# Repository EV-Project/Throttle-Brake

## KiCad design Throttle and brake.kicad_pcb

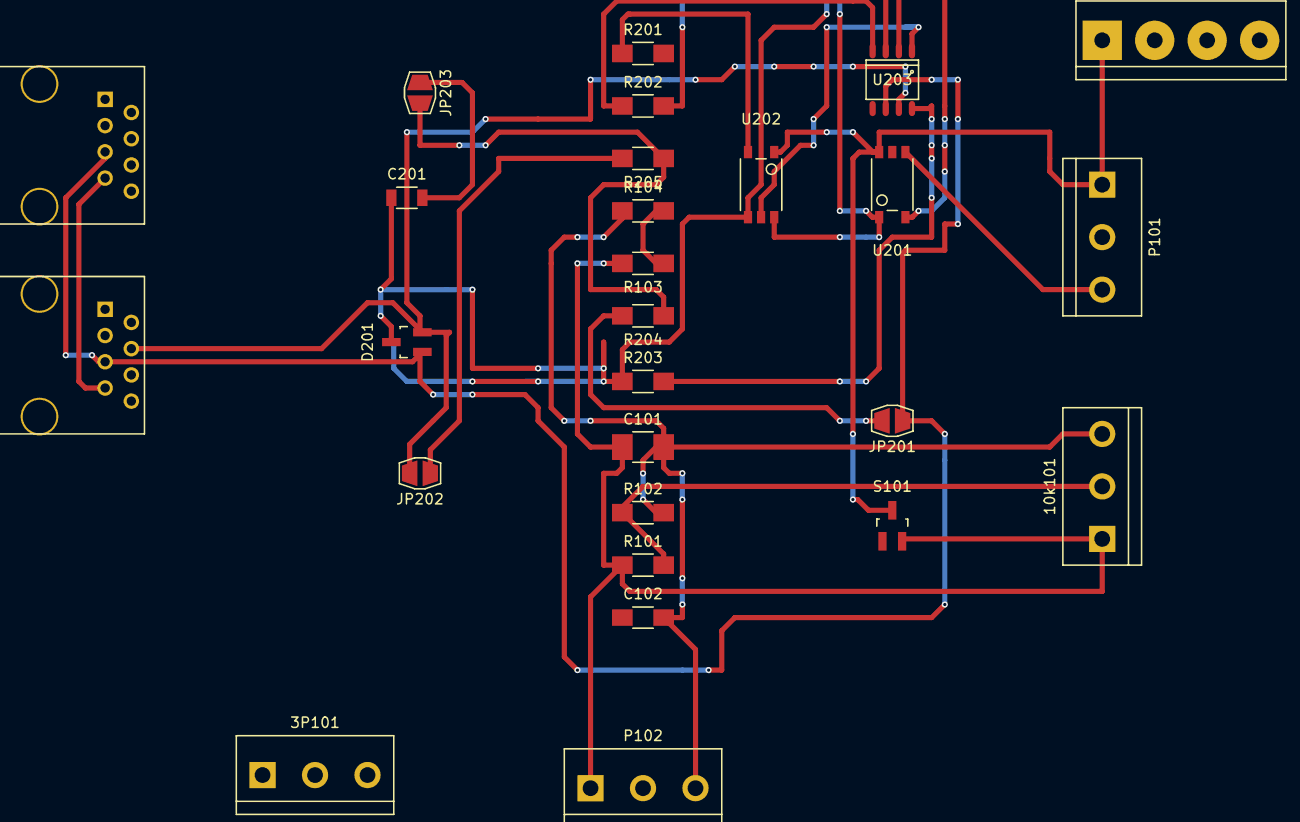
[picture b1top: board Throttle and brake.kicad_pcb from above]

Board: 2 copper layers, 27 parts (0 on the bottom side), 21 nets.

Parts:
3P101: Lever; bornier3
4P101: Ignition Switch; bornier4
10k101: POT; bornier3
C101: 10 uF; C_1210_HandSoldering
C102: 0.1 uF; C_1206_HandSoldering
C201: 4.7nF; C_1206
D201: PESD1CAN; SOT-23_Handsoldering
J201, J202: RJ45; RJ45_8
JP201, JP202: Terminate; JumperSingle
JP203: Filter; JumperSingle
P101: Pot connector; bornier3
P102: Throttle Pedal; bornier3
R101, R102: 1k; R_1206_HandSoldering
R103, R104, R201: 100; R_1206_HandSoldering
R202: 330; R_1206_HandSoldering
R203: 4.7K; R_1206_HandSoldering
R204, R205: 60; R_1206_HandSoldering
S101: Q_PNP_BCE; SOT-23_Handsoldering
U201, U202: TLP2361; soic-5
U203: MCP2551-I/SN; SO-8

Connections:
+3V3: 4P101.1, P101.1, S101.3, U201.6, U202.1
+5V: U201.1, U202.6, U203.3
/CANmodule/Aux+: J201.7, J202.7
/CANmodule/Aux-: J201.8, J202.8
/CANmodule/CAN_H: D201.2, J201.4, J202.4, JP202.1, U203.7
/CANmodule/CAN_L: D201.1, J201.5, J202.5, JP201.2, U203.6
GND: P101.3, U201.4
GNDA: 10k101.3, C101.2, C102.2, P102.3, R102.2, R104.1
GNDREF: C201.1, D201.3, R203.1, U202.4, U203.2
unnamed: 10k101.1, C101.1, P102.1, R101.1, R103.2, S101.2
unnamed: 10k101.2, R101.2, R102.1
unnamed: C201.2, JP203.2
unnamed: JP201.1, R204.2
unnamed: JP202.2, R205.2
unnamed: JP203.1, R204.1, R205.1
unnamed: R103.1, R104.2
unnamed: R201.1, U202.3
unnamed: R202.1, U203.4
unnamed: R202.2, U201.3
unnamed: R203.2, U203.8
unnamed: U202.5, U203.1

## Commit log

2016-11-08 version from flash drive
2016-11-08 added hx711 and organised schematic
2016-11-22 PCB layout
